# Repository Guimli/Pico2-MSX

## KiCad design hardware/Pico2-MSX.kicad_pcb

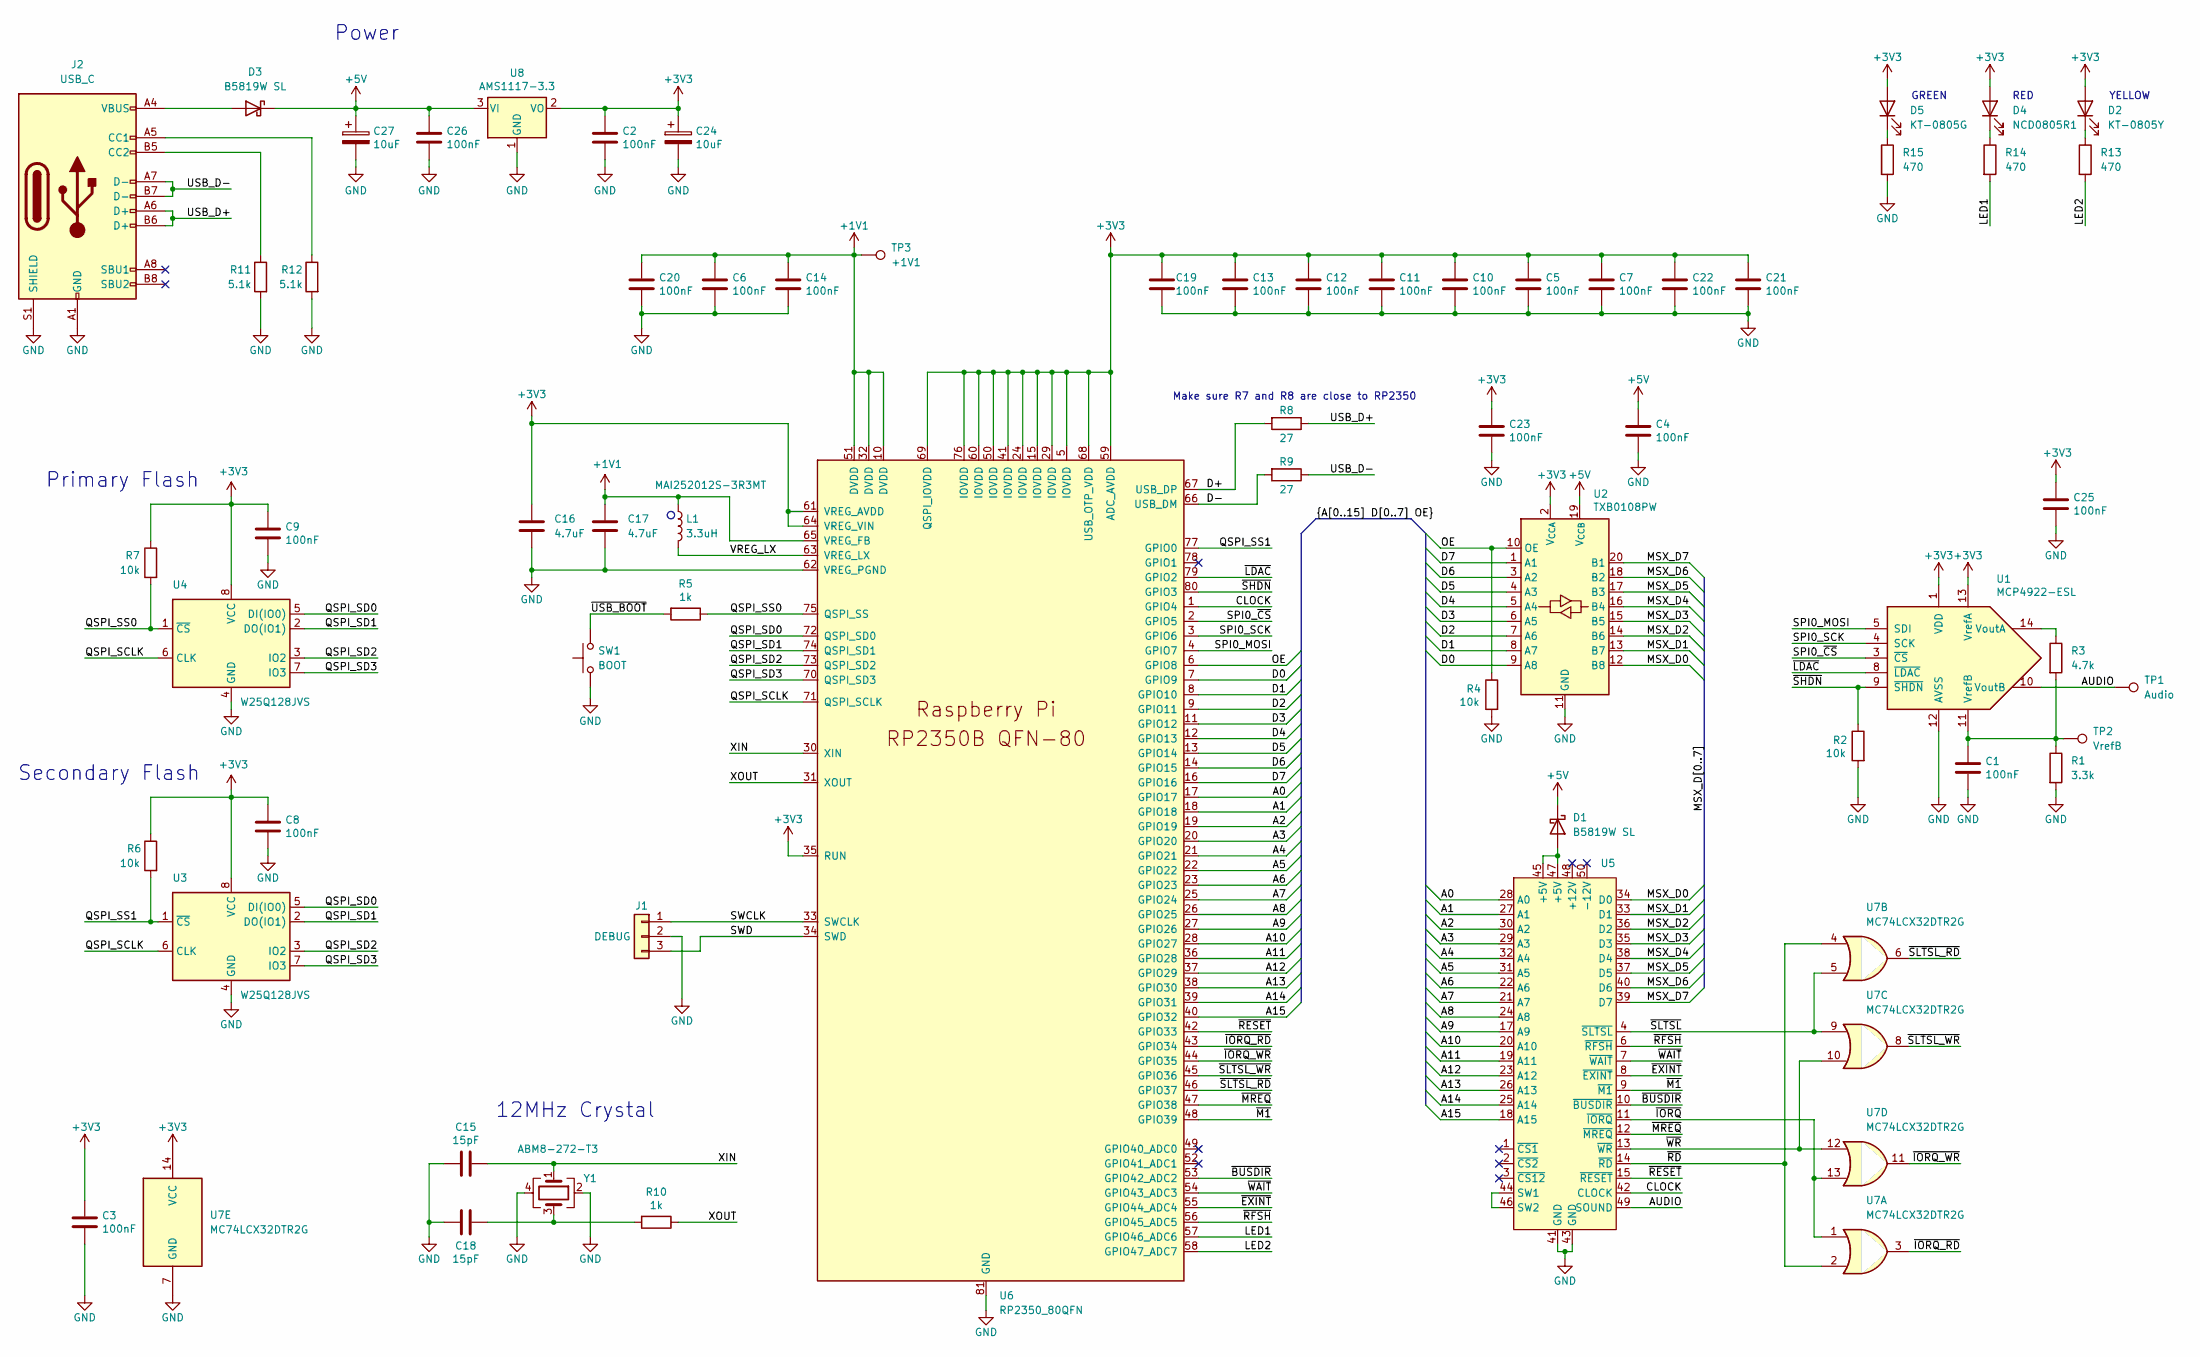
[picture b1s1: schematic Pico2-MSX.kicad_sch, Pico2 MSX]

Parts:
C1, C2, C3, C4, C8, C9, C23, C25, C26: 100nF; C_0402_1005Metric; LCSC C307331
C5, C6, C7, C10, C11, C12, C13, C14, C19, C20, C21, C22: 100nF; C_0402_1005Metric_thin; LCSC C307331
C15, C18: 15pF; C_0402_1005Metric; LCSC C1548
C16, C17: 4.7uF; C_0603_1608Metric_small; LCSC C19666
C24, C27: 10uF; CP_EIA-3216-18_Kemet-A; LCSC C7171
D1, D3: B5819W SL; D_SOD-123; LCSC C8598
D2: KT-0805Y; LED_0805_2012Metric; LCSC C2296
D4: NCD0805R1; LED_0805_2012Metric; LCSC C84256
D5: KT-0805G; LED_0805_2012Metric; LCSC C2297
J1: DEBUG; PinHeader_1x03_P1.27mm_Vertical; LCSC C24980
J2: USB_C; USB_C_Receptacle_G-Switch_GT-USB-7010ASV; LCSC C2988369
L1: 3.3uH; L_pol_2016; LCSC C520252
R1: 3.3k; R_0402_1005Metric; LCSC C25890
R2, R4, R6, R7: 10k; R_0402_1005Metric; LCSC C25744
R3: 4.7k; R_0402_1005Metric; LCSC C25900
R5, R10: 1k; R_0402_1005Metric; LCSC C11702
R8, R9: 27; R_0402_1005Metric; LCSC C25100
R11, R12: 5.1k; R_0402_1005Metric; LCSC C25905
R13, R14, R15: 470; R_0603_1608Metric; LCSC C23179
SW1: BOOT; SW_PUSH_6mm_H7.3mm
TP1: Audio; TestPoint_Pad_D2.5mm
TP2: VrefB; TestPoint_Pad_D2.5mm
TP3: +1V1; TestPoint_Pad_D2.5mm
U1: MCP4922-ESL; SOIC-14_3.9x8.7mm_P1.27mm; LCSC C39851
U2: TXB0108PW; TSSOP-20_4.4x6.5mm_P0.65mm; LCSC C53406
U3, U4: W25Q128JVS; SOIC-8_5.23x5.23mm_P1.27mm; LCSC C97521
U5: MSX_Cartridge
U6: RP2350_80QFN; RP2350-QFN-80-1EP_10x10_P0.4mm_EP3.4x3.4mm_ThermalVias; LCSC C9900138392
U7: MC74LCX32DTR2G; TSSOP-14_4.4x5mm_P0.65mm; LCSC C904104
U8: AMS1117-3.3; SOT-223-3_TabPin2; LCSC C6186
Y1: ABM8-272-T3; Crystal_SMD_3225-4Pin_3.2x2.5mm; LCSC C9002

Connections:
+1V1: C6.1, C14.1, C17.1, C20.1, L1.1, TP3.1, U6.10 (DVDD), U6.32 (DVDD), U6.51 (DVDD), U6.65 (VREG_FB)
+3V3: C2.1, C3.1, C5.1, C7.1, C8.1, C9.1, C10.1, C11.1, C12.1, C13.1, C16.1, C19.1, C21.1, C22.1, C23.1, C24.1, C25.1, D2.2 (A), D4.2 (A), D5.2 (A), R6.1, R7.1, U1.1 (VDD), U1.13 (VrefA), U2.2 (V_{CCA}), U3.8 (VCC), U4.8 (VCC), U6.5 (IOVDD), U6.15 (IOVDD), U6.24 (IOVDD), U6.29 (IOVDD), U6.35 (RUN), U6.41 (IOVDD), U6.50 (IOVDD), U6.59 (ADC_AVDD), U6.60 (IOVDD), U6.61 (VREG_AVDD), U6.64 (VREG_VIN), U6.68 (USB_OTP_VDD), U6.69 (QSPI_IOVDD), U6.76 (IOVDD), U7.14 (VCC), U8.2 (VO)
+5V: C4.1, C26.1, C27.1, D1.1 (K), D3.1 (K), U2.19 (V_{CCB}), U8.3 (VI)
/A0: U5.28 (A0), U6.17 (GPIO17)
/A1: U5.27 (A1), U6.18 (GPIO18)
/A2: U5.30 (A2), U6.19 (GPIO19)
/A3: U5.29 (A3), U6.20 (GPIO20)
/A4: U5.32 (A4), U6.21 (GPIO21)
/A5: U5.31 (A5), U6.22 (GPIO22)
/A6: U5.22 (A6), U6.23 (GPIO23)
/A7: U5.21 (A7), U6.25 (GPIO24)
/A8: U5.24 (A8), U6.26 (GPIO25)
/A9: U5.17 (A9), U6.27 (GPIO26)
/A10: U5.20 (A10), U6.28 (GPIO27)
/A11: U5.19 (A11), U6.36 (GPIO28)
/A12: U5.23 (A12), U6.37 (GPIO29)
/A13: U5.26 (A13), U6.38 (GPIO30)
/A14: U5.25 (A14), U6.39 (GPIO31)
/A15: U5.18 (A15), U6.40 (GPIO32)
/AUDIO: TP1.1, U1.10 (VoutB), U5.49 (SOUND)
/CLOCK: U5.42 (CLOCK), U6.1 (GPIO4)
/D0: U2.9 (A8), U6.7 (GPIO9)
/D1: U2.8 (A7), U6.8 (GPIO10)
/D2: U2.7 (A6), U6.9 (GPIO11)
/D3: U2.6 (A5), U6.11 (GPIO12)
/D4: U2.5 (A4), U6.12 (GPIO13)
/D5: U2.4 (A3), U6.13 (GPIO14)
/D6: U2.3 (A2), U6.14 (GPIO15)
/D7: U2.1 (A1), U6.16 (GPIO16)
/D+: R8.2, U6.67 (USB_DP)
/D-: R9.2, U6.66 (USB_DM)
/LED1: R14.2, U6.57 (GPIO46_ADC6)
/LED2: R13.2, U6.58 (GPIO47_ADC7)
/MSX_D0: U2.12 (B8), U5.34 (D0)
/MSX_D1: U2.13 (B7), U5.33 (D1)
/MSX_D2: U2.14 (B6), U5.36 (D2)
/MSX_D3: U2.15 (B5), U5.35 (D3)
/MSX_D4: U2.16 (B4), U5.38 (D4)
/MSX_D5: U2.17 (B3), U5.37 (D5)
/MSX_D6: U2.18 (B2), U5.40 (D6)
/MSX_D7: U2.20 (B1), U5.39 (D7)
/OE: R4.1, U2.10 (OE), U6.6 (GPIO8)
/QSPI_SCLK: U3.6 (CLK), U4.6 (CLK), U6.71 (QSPI_SCLK)
/QSPI_SD0: U3.5 (DI(IO0)), U4.5 (DI(IO0)), U6.72 (QSPI_SD0)
/QSPI_SD1: U3.2 (DO(IO1)), U4.2 (DO(IO1)), U6.74 (QSPI_SD1)
/QSPI_SD2: U3.3 (IO2), U4.3 (IO2), U6.73 (QSPI_SD2)
/QSPI_SD3: U3.7 (IO3), U4.7 (IO3), U6.70 (QSPI_SD3)
/QSPI_SS0: R5.1, R7.2, U4.1 (~CS), U6.75 (QSPI_SS)
/QSPI_SS1: R6.2, U3.1 (~CS), U6.77 (GPIO0)
/SPI0_MOSI: U1.5 (SDI), U6.4 (GPIO7)
/SPI0_SCK: U1.4 (SCK), U6.3 (GPIO6)
/SPI0_~CS: U1.3 (~CS), U6.2 (GPIO5)
/SWCLK: J1.1, U6.33 (SWCLK)
/SWD: J1.3, U6.34 (SWD)
/USB_D+: J2.A6 (D+), J2.B6 (D+), R8.1
/USB_D-: J2.A7 (D-), J2.B7 (D-), R9.1
/VREG_LX: L1.2, U6.63 (VREG_LX)
/XIN: C15.1, U6.30 (XIN), Y1.1
/XOUT: R10.1, U6.31 (XOUT)
/~BUSDIR: U5.10 (~BUSDIR), U6.53 (GPIO42_ADC2)
/~EXINT: U5.8 (~EXINT), U6.55 (GPIO44_ADC4)
/~IORQ_RD: U6.43 (GPIO34), U7.3
/~IORQ_WR: U6.44 (GPIO35), U7.11
/~IORQ: U5.11 (~IORQ), U7.1, U7.13
/~LDAC: U1.8 (~LDAC), U6.79 (GPIO2)
/~M1: U5.9 (~M1), U6.48 (GPIO39)
/~MREQ: U5.12 (~MREQ), U6.47 (GPIO38)
/~RD: U5.14 (~RD), U7.2, U7.4
/~RESET: U5.15 (~RESET), U6.42 (GPIO33)
/~RFSH: U5.6 (~RFSH), U6.56 (GPIO45_ADC5)
/~SHDN: R2.1, U1.9 (~SHDN), U6.80 (GPIO3)
/~SLTSL_RD: U6.46 (GPIO37), U7.6
/~SLTSL_WR: U6.45 (GPIO36), U7.8
/~SLTSL: U5.4 (~SLTSL), U7.5, U7.9
/~USB_BOOT: R5.2, SW1.2
/~WAIT: U5.7 (~WAIT), U6.54 (GPIO43_ADC3)
/~WR: U5.13 (~WR), U7.10, U7.12
GND: C1.2, C2.2, C3.2, C4.2, C5.2, C6.2, C7.2, C8.2, C9.2, C10.2, C11.2, C12.2, C13.2, C14.2, C15.2, C16.2, C17.2, C18.2, C19.2, C20.2, C21.2, C22.2, C23.2, C24.2, C25.2, C26.2, C27.2, J1.2, J2.A1 (GND), J2.A12 (GND), J2.B1 (GND), J2.B12 (GND), J2.S1 (SHIELD), R1.2, R2.2, R4.2, R11.2, R12.2, R15.2, SW1.1, U1.12 (AVSS), U2.11 (GND), U3.4 (GND), U4.4 (GND), U5.41 (GND), U5.43 (GND), U6.62 (VREG_PGND), U6.81 (GND), U7.7 (GND), U8.1 (GND), Y1.2, Y1.4
unnamed: C18.1, R10.2, Y1.3
unnamed: D1.2 (A), U5.45 (+5V), U5.47 (+5V)
unnamed: D2.1 (K), R13.1
unnamed: D3.2 (A), J2.A4 (VBUS), J2.A9 (VBUS), J2.B4 (VBUS), J2.B9 (VBUS)
unnamed: D4.1 (K), R14.1
unnamed: D5.1 (K), R15.1
unnamed: J2.A5 (CC1), R12.1
unnamed: J2.B5 (CC2), R11.1
unnamed: R3.1, U1.14 (VoutA)
unnamed: C1.1, R1.1, R3.2, TP2.1, U1.11 (VrefB)
unnamed: U5.44 (SW1), U5.46 (SW2)

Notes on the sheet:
12MHz Crystal
RED
Primary Flash
YELLOW
Make sure R7 and R8 are close to RP2350
Secondary Flash
Power
GREEN

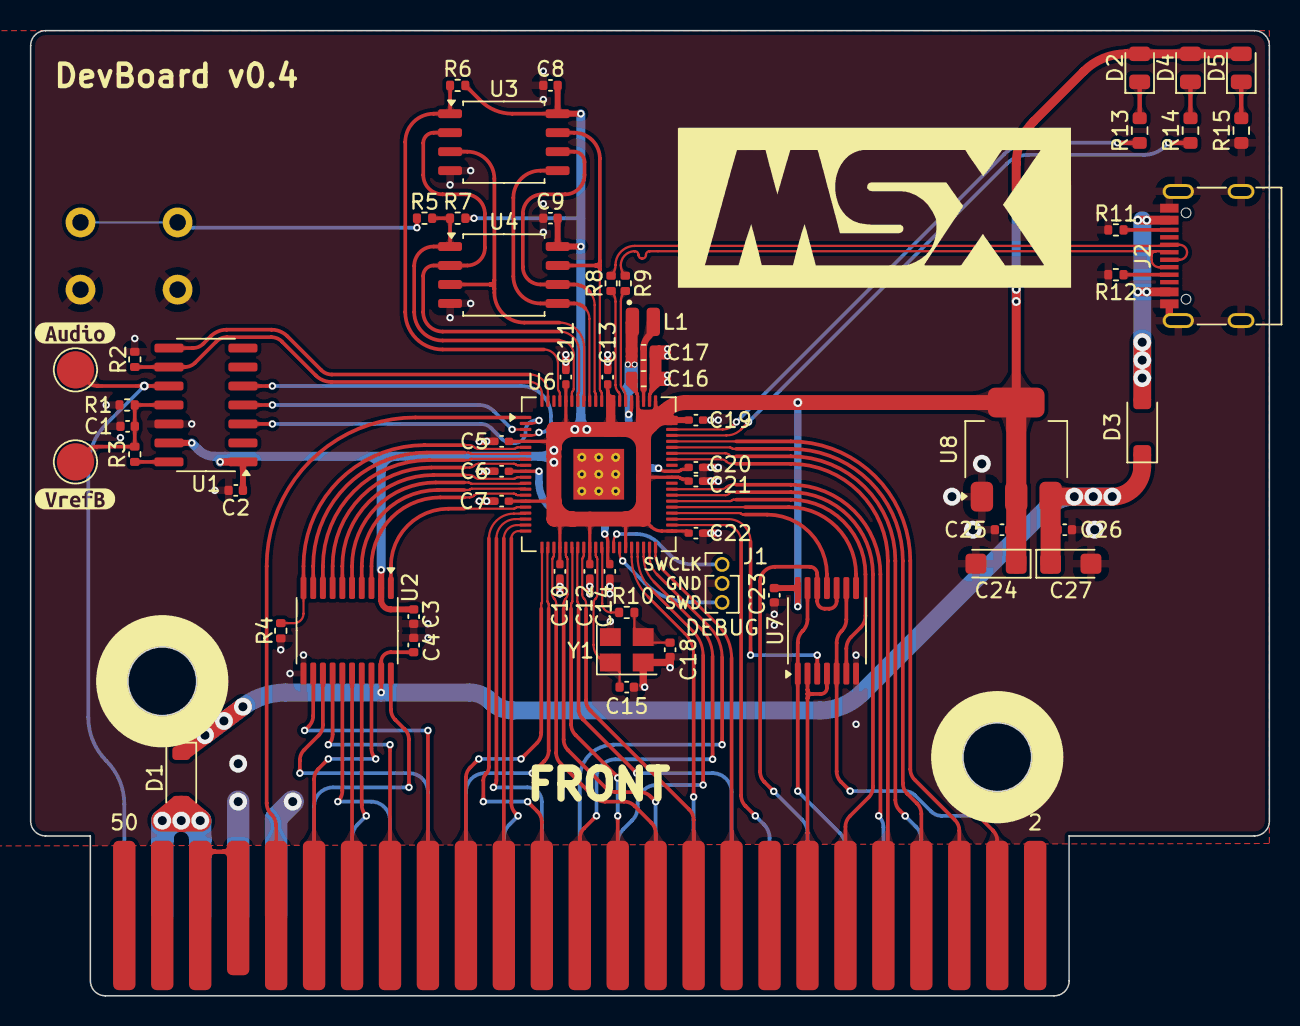
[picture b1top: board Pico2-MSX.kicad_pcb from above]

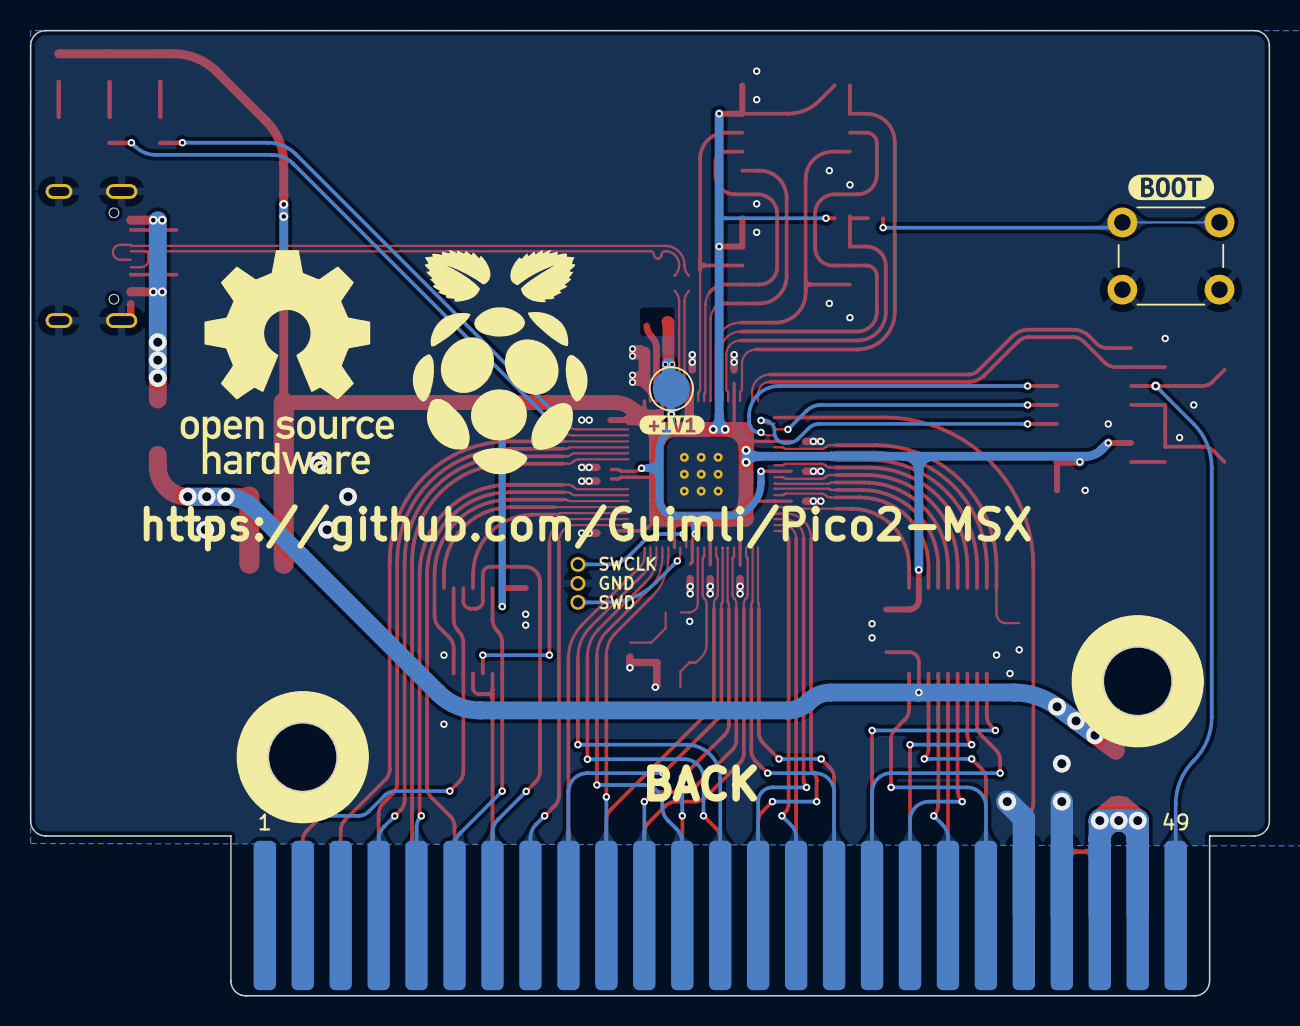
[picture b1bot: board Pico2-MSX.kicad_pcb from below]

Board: 4 copper layers, 82.9 x 64.6 mm, 67 parts (4 on the bottom side), 89 nets.

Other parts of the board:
kibuzzard-671CD39D: G***; kibuzzard-671CD39D
kibuzzard-671CD351: G***; kibuzzard-671CD351
kibuzzard-671CD378: G***; kibuzzard-671CD378
kibuzzard-671CD496: G***; kibuzzard-671CD496

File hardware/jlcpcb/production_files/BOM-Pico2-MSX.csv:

Comment,Designator,Footprint,LCSC,Quantity
1k,"R10,R5",R_0402_1005Metric,C11702,2
15pF,"C15,C18",C_0402_1005Metric,C1548,2
4.7uF,"C16,C17",C_0603_1608Metric_small,C19666,2
KT-0805Y,D2,LED_0805_2012Metric,C2296,1
KT-0805G,D5,LED_0805_2012Metric,C2297,1
470,"R13,R14,R15",R_0603_1608Metric,C23179,3
DEBUG,J1,PinHeader_1x03_P1.27mm_Vertical,C24980,1
27,"R8,R9",R_0402_1005Metric,C25100,2
10k,"R2,R4,R6,R7",R_0402_1005Metric,C25744,4
3.3k,R1,R_0402_1005Metric,C25890,1
4.7k,R3,R_0402_1005Metric,C25900,1
5.1k,"R11,R12",R_0402_1005Metric,C25905,2
USB_C,J2,USB_C_Receptacle_G-Switch_GT-USB-7010ASV,C2988369,1
100nF,"C1,C10,C11,C12,C13,C14,C19,C2,C20,C21,C22,C23,C25,C26,C3,C4,C5,C6,C7,C8,C9",C_0402_1005Metric,C307331,21
MCP4922-ESL,U1,SOIC-14_3.9x8.7mm_P1.27mm,C39851,1
3.3uH,L1,L_pol_2016,C520252,1
TXB0108PW,U2,TSSOP-20_4.4x6.5mm_P0.65mm,C53406,1
AMS1117-3.3,U8,SOT-223-3_TabPin2,C6186,1
10uF,"C24,C27",CP_EIA-3216-18_Kemet-A,C7171,2
NCD0805R1,D4,LED_0805_2012Metric,C84256,1
B5819W SL,"D1,D3",D_SOD-123,C8598,2
ABM8-272-T3,Y1,Crystal_SMD_3225-4Pin_3.2x2.5mm,C9002,1
MC74LCX32DTR2G,U7,TSSOP-14_4.4x5mm_P0.65mm,C904104,1
W25Q128JVS,"U3,U4",SOIC-8_5.23x5.23mm_P1.27mm,C97521,2
RP2350_80QFN,U6,RP2350-QFN-80-1EP_10x10_P0.4mm_EP3.4x3.4mm_ThermalVias,C9900138392,1

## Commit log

2024-10-25 Improving the 1v1 circuit
2024-10-28 Some optimizations
2024-11-14 Delete via for flash memory
    And other small modifications (reference at JLCPCB)
2024-11-30 Cost reduction and correction of fixing hole placement
    - The via are now at a minimum hole size of 0.25.
    - The 0201 capacitors have been replaced by 0402s.
    - The fixing holes have been moved to a position closer to the standard.
    - The tracks have been widened outside the RP2350 area.
